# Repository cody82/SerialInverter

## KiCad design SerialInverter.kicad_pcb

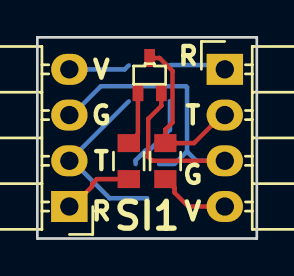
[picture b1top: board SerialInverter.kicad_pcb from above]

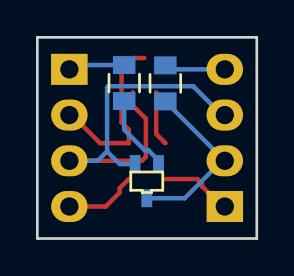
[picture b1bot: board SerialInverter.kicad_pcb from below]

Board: 2 copper layers, 12.2 x 11.2 mm, 8 parts (3 on the bottom side), 9 nets.

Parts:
P1, P4: CONN_01X04; Pin_Header_Angled_1x04
P2: TRANSISTOR1; SOT-323
P3: TRANSISTOR2; SOT-323
R1, R2, R3, R4: R; C_0805

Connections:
/RX1: P1.1, R1.2
/RX2: P4.1, R2.2
/TX1: P1.2, P3.3, R4.2
/TX2: P2.3, P4.2, R3.2
GND: P1.3, P2.2, P3.2, P4.3
unnamed: P2.1, R1.1
unnamed: P3.1, R2.1
VCC: P1.4, R4.1
VDD: P4.4, R3.1

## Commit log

2016-07-29 First version ordered.
